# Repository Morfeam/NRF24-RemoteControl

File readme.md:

# NRF24-Nano Remote Control

## Summary

- A rudimentary RC controller used to read movements of joysticks and write them wirelessly to a RC Car.

### Backstory

- In order to prepare for more advanced RF projects in the future, it was necessary to understand the basics of the NRF24 module, how it works, and where it falls short. For the code, designs, and circuit listed in this project, the RC controller is writing joystick movement data to drive an RC car project that's still in development (for now ;D).

### Reading Joystick Movements

- With 2 joysticks there are 4 different channels of movement we can read in to pass over radio communication:
  - Left vertical (left to right), left horizontal (up and down), right vertical (left to right), and right horizontal (up and down)
  - The Arduino nano's [analog to digital converter (ADC)](https://en.wikipedia.org/wiki/Analog-to-digital_converter) has a 10-bit resolution, we can take in a analog reading between 0 - 1024 for each channel listed above.

- Values for each channel are mapped from 0 - 1024 to 0 - 255 for ease of use by the RC receiver on the end of the serial connection (in this example, PWM values to drive an RC car).

- Given the orientation of the joysticks are being flipped to simplify wiring and space, when the values are being mapped, we invert the values for left horizontal and right vertical.
 - This is done by subtracting the max 'ceiling' value for said channel by the channel value mapped from the analog reading (255 - channel mapped value).

### NRF24 Communication

- The NRF24 module uses a 2.4 GHz frequency to communicate with other NRF24 module(s). This is represented in code where two devices would form a connection by opening either a read or write pipe that matches the other modules byte address.

- The NRF24 uses the SPI protocol to transmit and receive data between the arduino nano, where in this example, the arduino drives the NRF24 module to transmit packets to the configured address. The packets here being the struct `data` where the 4 joysticks channels are represented and sent to the configured address.
  - See [Serial Peripheral Interface](https://en.wikipedia.org/wiki/Serial_Peripheral_Interface) for more details on this protocol.

### Output To Display

  OLED display uses I2C protocol and serial communication is handled via the `Adafruit_SSD1306` library to write relevant data to display.

  Display data key:

  LV: *Left vertical joystick value*

  LH: *Left horizontal joystick value*

  RV: *Right vertical joystick value*

  RH: *Right horizontal joystick value*

## Material List

- 1x 50mm x 70mm PCB Prototype Board
- 22 AWG Jumper Wires
- 1x Arduino Nano (ATmega328P)
- 1x NRF24 Transceiver Module 2.4G
- 1x NRF24 Socket Adapter Board
- 2x dual-axis joysticks
- DC switch (250V 10A switch is what I'm using)
- 1x small OLED display (I2C)
- Soldering setup (iron, solder, etc.)
- 9 volt battery + battery connector

#### Optional Materials

- Heat shrink tubing
- 3d printer and PLA filament (for printing the housing)
- Solder flux paste to make better contacts

## Future Enhancements

- Setting up reading pipe on RC controller
  - NRF24 transceiver is capable of both reading and writing data to a multitude of addresses.
  - Setting up a reading data pipeline, it would be possible to interpret payloads from the devices that are being written to, such as the end device's cameras, sensors, etc.

- Read and write to multiple devices
  - Writing to multiple address allows to control two devices with the same or potentially different payloads
  - In tandem with reading and writing, the RC controller could be used as a central hub in the RF network to relay and interpret information from one node to another, simplifying computation / logic required at each end node device.

- Bluetooth and wifi connectivity
  - The RC controller could pass information off to other devices over another local network not associated with the NRF24 2.4 Ghz band.
  - The RC controller could be used as a go between the RF devices and cloud infrastructure, which could host communication to or from a private web api hosted in the cloud.

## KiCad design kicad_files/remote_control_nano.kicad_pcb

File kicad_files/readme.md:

# NRF24-Nano Remote Control - KiCad Files and Circuit Diagrm

### Circuit Diagram (Schematic):

### PCB Layout:

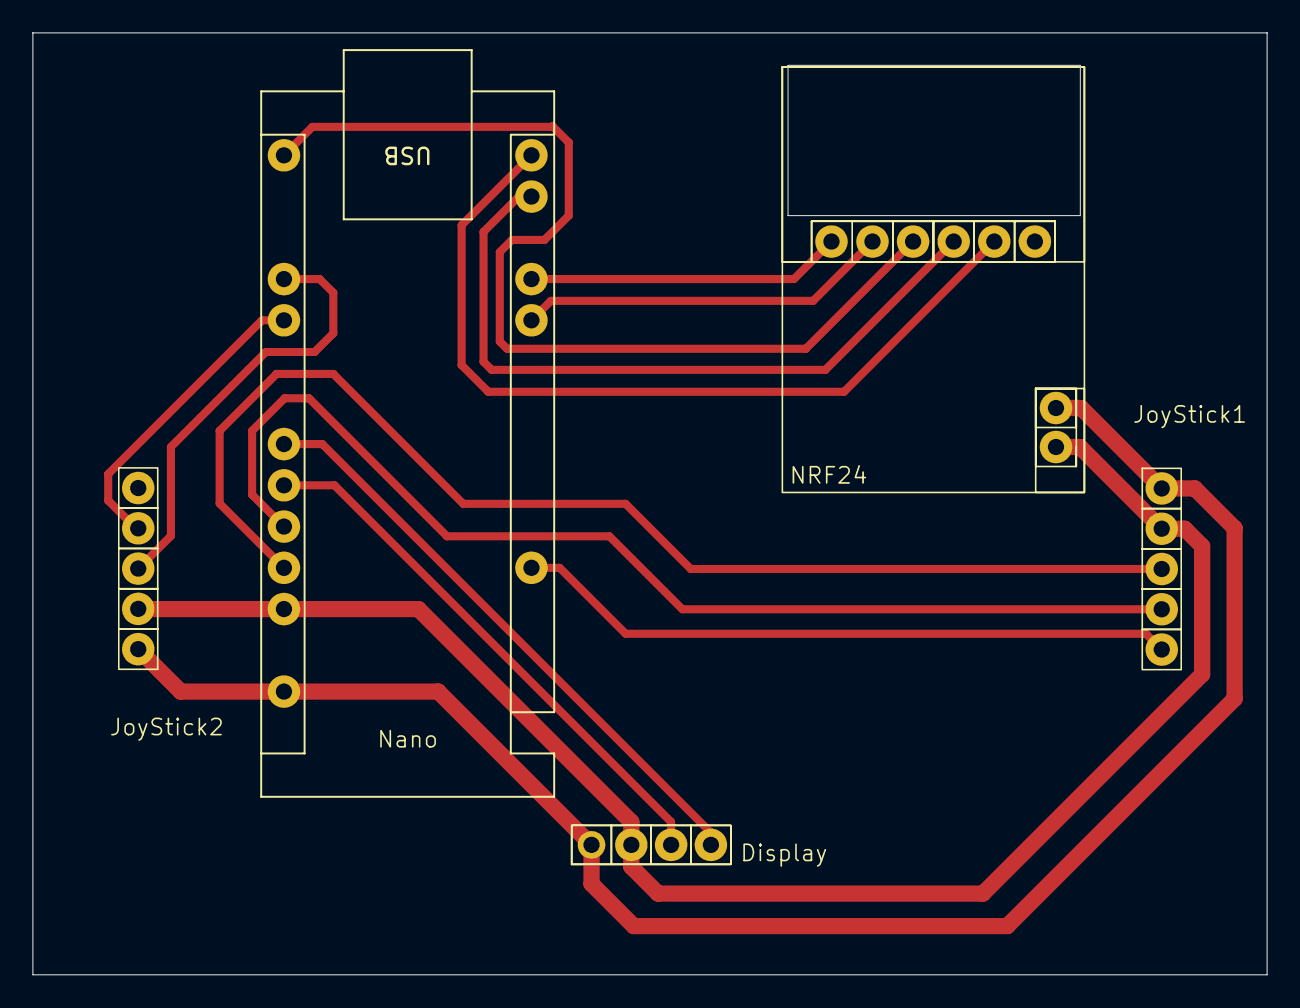
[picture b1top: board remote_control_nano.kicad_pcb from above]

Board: 2 copper layers, 76.0 x 58.0 mm, 5 parts (0 on the bottom side), 14 nets.

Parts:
JoyStick1, JoyStick2: JoyStick
NRF24: NRF24L01_Breakout; NRF24_Breakout
Nano: Arduino_Nano_v3.x; Arduino_Nano
OLED_display1: OLED_display

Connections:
unnamed: JoyStick1.2 (VCC), JoyStick2.2 (VCC), NRF24.2 (VCC), Nano.27 (+5V), OLED_display1.2 (VCC)
unnamed: JoyStick2.3 (VRx), Nano.19 (A0)
unnamed: JoyStick2.4 (VRy), Nano.20 (A1)
unnamed: Nano.23 (A4), OLED_display1.4 (SDA)
unnamed: Nano.24 (A5), OLED_display1.3 (SCL)
unnamed: JoyStick1.4 (VRy), Nano.25 (A6)
unnamed: JoyStick1.3 (VRx), Nano.26 (A7)
unnamed: JoyStick1.5 (SW), Nano.5 (D2)
unnamed: NRF24.4 (~CSN), Nano.11 (D8)
unnamed: NRF24.3 (CE), Nano.12 (D9)
unnamed: NRF24.6 (MOSI), Nano.14 (D11)
unnamed: NRF24.7 (MISO), Nano.15 (D12)
unnamed: NRF24.5 (SCK), Nano.16 (D13)
unnamed: JoyStick1.1 (GND), JoyStick2.1 (GND), NRF24.1 (GND), Nano.29 (GND), OLED_display1.1 (GND)

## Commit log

2025-07-09 migrate local project to github
2025-07-10 Update main readme
2025-07-11 add 3d models for case and kicad project files
